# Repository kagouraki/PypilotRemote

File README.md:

# Pypilot Remote

## Overview

**Pypilot Remote** is a Wi-Fi remote control and display for the  
[pypilot](https://github.com/pypilot/pypilot) open-source marine autopilot by Sean D’Epagnier.

It connects to a pypilot server in client mode and provides a **clean, dedicated hardware interface**
to control the autopilot and display essential navigation and system information.

The project is currently housed in a **Raymarine ST70 autopilot display**, giving new life to legacy
marine hardware. The design is intentionally adaptable so it can be reused with other discontinued
or surplus commercial enclosures.

A future goal is a **custom 3D-printed enclosure**, which would make the project more accessible
without relying on expensive legacy hardware. This will require additional work around waterproof
screen mounting, buttons, and connectors.

---

## Hardware

- **MCU:** ESP32-S3 N16R8 with external antenna  
- **Display:** 3.47" transflective color LCD  
  - Resolution: 480×320  
  - Model: UEED035HV-RX40-L001B (Viewe)  
- **Input:** 9 physical pushbuttons (no touchscreen)
- **Power input:** 10–18 V DC
- **Programming:**  
  - USB (without opening the enclosure)  
  - OTA (Over-The-Air updates)

---

## Software & Design Tools

- **Firmware:** ESP32 (Arduino framework)
- **IDE:** Eclipse Sloeber
- **Hardware design:** KiCad v9
- **License:** GPL-3.0-only

---

## Features

- Connects to a pypilot server or creates an AP for configuration
- Autopilot **Auto / Standby** control
- Steering mode selection
- Course changes in Auto mode:
  - −1°, −10°, +1°, +10°
- Adjustable backlight for screen and buttons
- Light and dark UI themes
- Information screens:
  - Pypilot data
  - Device status
- Scrollable console log
- “Return to previous heading” Auto command
- Persistent configuration stored in EEPROM
- Robust Wi-Fi and TCP reconnection handling
- Visual Wi-Fi status indicator

---

## Button Functions

### Autopilot Control
- **Standby**  
  Disengages the autopilot

- **Auto**  
  Engages the autopilot and commands the current heading

- **Auto (long press > 3 s)**  
  Engages autopilot using the **previous heading command**

### Course Adjustment
- **−1** → Port 1°  
- **−10** → Port 10°  
- **+1** → Starboard 1°  
- **+10** → Starboard 10°

### Mode & Interface
- **Mode**  
  Cycles through available steering modes

- **Backlight**  
  Toggles backlight on/off

- **Backlight (long press > 10 s)**  
  Forces AP mode

- **Info**  
  Cycles through information screens and returns to home

- **Backlight + Mode (long press > 5 s)**  
  Restarts the Pypilot Remote

### Notes
- When **not on the home screen**, only **Auto** and **Standby** are active
- On the console log screen:
  - **+1 / +10** scroll up and down

---

## Connection Logic

1. On boot, the device attempts to connect to the configured Wi-Fi SSID  
   → Wi-Fi icon flashes **RED**
2. After the configured number of retries:
   - If unsuccessful → switches to **AP mode** (Wi-Fi icon **YELLOW**)
3. Once Wi-Fi is connected:
   - Tries to connect to the pypilot TCP server indefinitely  
   → Wi-Fi icon flashes **GREEN**
4. When connected to pypilot:
   - Wi-Fi icon becomes **solid GREEN**
   - Device is fully operational

---

## Configuration Web Interface

When in **AP mode**, access the configuration interface at:

```
http://192.168.4.1
```

### Available Settings

- **WiFi SSID** – Network to connect to
- **WiFi Password**
- **Max WiFi Retries** – Attempts before falling back to AP mode
- **Pypilot IP** – IP address of the pypilot server
- **TCP Port** – Default: `23322`
- **UDP Port** – Not used
- **Brightness (Backlight Off)** – 0–255
- **Brightness (Backlight On)** – 0–255
- **Key Backlight Brightness** – 0–255
- **Start Theme** – Theme when backlight is off
- **Backlight Theme** – Theme when backlight is on
- **Rescan Wi-Fi** – Refresh available networks
- **OTA Update** – Upload firmware `.bin` file

---

## Electrical Connections

The device uses **4 pins** from the SeatalkNG connector:

| Color | Signal |
|-----|-------|
| Red | +12 V |
| Black | GND |
| Blue | D+ |
| White | D− |

### Important Warning

⚠️ **DO NOT CONNECT TO A SEATALKNG NETWORK**

- Blue and white lines are **CAN-H / CAN-L**
- Connecting them to the ESP32 **will destroy the MCU**

### USB Programming (Optional)

For USB programming or debugging:
- Splice a USB cable
- Connect **D+**, **D−**, and **GND**
- A serial port will appear on the host computer

---

## Assembly

You can find the assembly guide here 
[assembly wiki](https://github.com/kagouraki/PypilotRemote/wiki/Assembly)

---

## Video

📺 **Demo video:**  

[Interface and funtionality video](https://youtu.be/A5Dgf8vR-sQ)

---

## License

This project is licensed under the  
**GNU General Public License v3.0 (GPL-3.0-only)**.

See the `LICENSE` file for details.

---

## Contributing

Contributions, improvements, and adaptations to other hardware platforms
are welcome — as long as they respect the GPL.

Let’s keep open source alive.

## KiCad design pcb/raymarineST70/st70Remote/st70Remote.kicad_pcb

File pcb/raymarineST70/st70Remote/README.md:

# PCB / Hardware Design

This directory contains the **PCB design files** for the **Pypilot Remote** hardware.

The board is designed using **KiCad v9** and is intended to be manufactured using standard PCB
fabrication and assembly services.

---

## Design Tools

- **EDA software:** KiCad v9  
- **Project files:** Native KiCad schematic and PCB files  
- **Units:** Metric

---

## Manufacturing

### PCB Fabrication
- The PCB was ordered and manufactured using **JLCPCB**

### Component Sourcing
- All electronic components were sourced from **LCSC**
- Component details and ordering information are provided in:

```
LCSCpartNum.csv
```

This file contains LCSC part numbers and additional information useful for ordering parts.

---

## Assembly Notes

### SeatalkNG Connector

The SeatalkNG connector is **not a standard off-the-shelf part**.

To populate it:
- Desolder one of the two SeatalkNG connectors from a **stock Raymarine ST70 PCB**
- Solder the recovered connector onto the **Pypilot Remote PCB**

This approach was chosen to ensure mechanical compatibility with the original enclosure.

---

### 3D Printed Parts

A **3D-printed adapter for the LCD screen** is required.

- The adapter files are located in the `3dparts/` directory
- It is used to correctly position and secure the display within the enclosure

---

### Double-Sided Assembly

- The PCB uses **components on both top and bottom layers**
- This may be more challenging for home assembly, but it is feasible

---

## Notes

- The PCB design is closely tied to the enclosure and mechanical layout
- Modifications may be required if adapting the design to a different housing

---

## License

The PCB design is released under the  
**GNU General Public License v3.0 (GPL-3.0-only)**.

See the `LICENSE` file in the root of the repository for details.

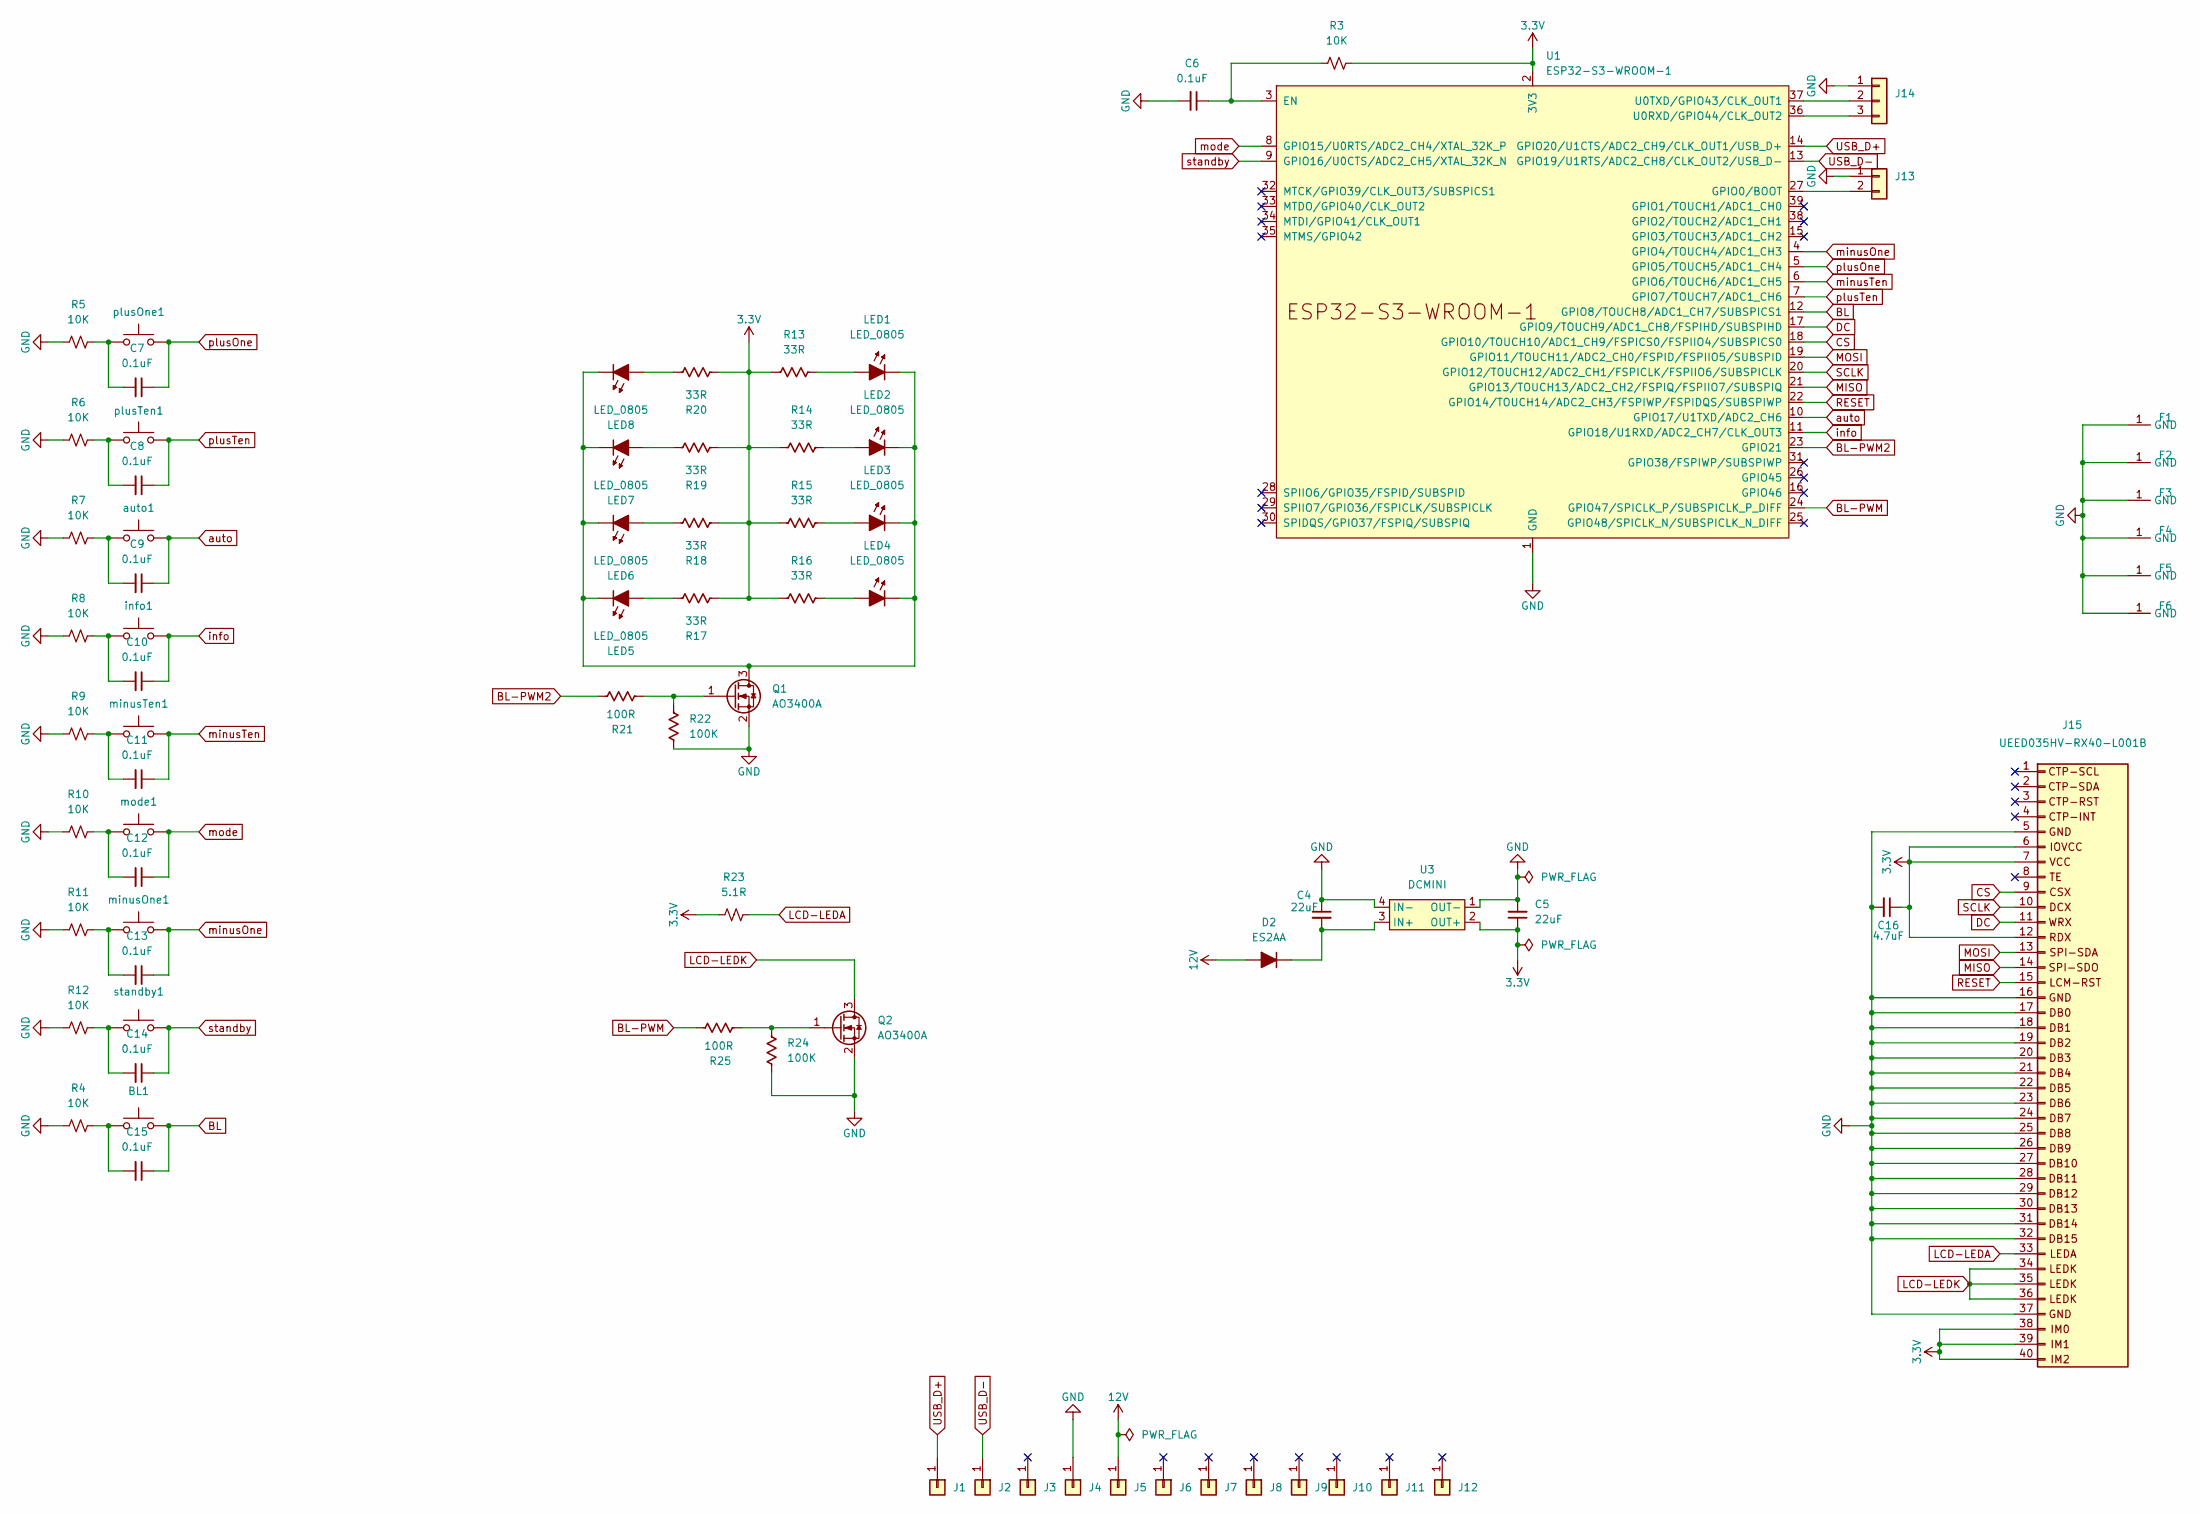
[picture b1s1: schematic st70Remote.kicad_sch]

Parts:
BL1: SMD_6.2x6.2mm_h7.0mm; Push_SMD_6.2x6.2mm; Mfg Part# 679-2384-2-ND
C4, C5: 22uF; C_1206_3216Metric_Pad1.42x1.75mm; Voltage 25V; Tolerance 10%
C6, C7, C8, C9, C10, C11, C12, C13, C14, C15: 0.1uF; C_0805_2012Metric; Voltage 25V; Tolerance 5%
C16: 4.7uF; C_0805_2012Metric; Voltage 25V; Tolerance 5%
D2: ES2AA; D_SMA
F1, F2, F3, F4, F5, F6: Harwin S1791-42R
J1, J2, J3, J4, J5, J6, J7, J8, J9, J10, J11, J12: Conn_01x01; 1x01_P2.54mm
J13: Conn_01x02; 1x02_P2.54mm
J14: Conn_01x03; 1x03_P2.54mm_Locking
J15: UEED035HV-RX40-L001B; XUNPU FPC-05F-40PH20
LED1, LED2, LED3, LED4, LED5, LED6, LED7, LED8: LED_0805; LED_0805_2012Metric
Q1, Q2: AO3400A; SOT-23
R3, R4, R5, R6, R7, R8, R9, R10, R11, R12: 10K; R_0805_2012Metric
R13, R14, R15, R16, R17, R18, R19, R20: 33R; R_0805_2012Metric
R21, R25: 100R; R_0805_2012Metric
R22, R24: 100K; R_0805_2012Metric
R23: 5.1R; R_0805_2012Metric
U1: ESP32-S3-WROOM-1; ESP32-S3-WROOM-1U
U3: DCMINI
auto1: SMD_6.2x6.2mm_h7.0mm; Push_SMD_6.2x6.2mm; Mfg Part# 679-2384-2-ND
info1: SMD_6.2x6.2mm_h7.0mm; Push_SMD_6.2x6.2mm; Mfg Part# 679-2384-2-ND
minusOne1: SMD_6.2x6.2mm_h7.0mm; Push_SMD_6.2x6.2mm; Mfg Part# 679-2384-2-ND
minusTen1: SMD_6.2x6.2mm_h7.0mm; Push_SMD_6.2x6.2mm; Mfg Part# 679-2384-2-ND
mode1: SMD_6.2x6.2mm_h7.0mm; Push_SMD_6.2x6.2mm; Mfg Part# 679-2384-2-ND
plusOne1: SMD_6.2x6.2mm_h7.0mm; Push_SMD_6.2x6.2mm; Mfg Part# 679-2384-2-ND
plusTen1: SMD_6.2x6.2mm_h7.0mm; Push_SMD_6.2x6.2mm; Mfg Part# 679-2384-2-ND
standby1: SMD_6.2x6.2mm_h7.0mm; Push_SMD_6.2x6.2mm; Mfg Part# 679-2384-2-ND

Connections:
3.3V: C5.1, C16.1, J15.6, J15.7, J15.12, J15.38, J15.39, J15.40, R3.1, R13.1, R14.1, R15.1, R16.1, R17.1, R18.1, R19.1, R20.1, R23.2, U1.2 (3V3), U3.2 (OUT+)
12V: D2.2 (A), J5.1
BL: BL1.2, C15.1, U1.12 (GPIO8/TOUCH8/ADC1_CH7/SUBSPICS1)
BL-PWM: R25.2, U1.24 (GPIO47/SPICLK_P/SUBSPICLK_P_DIFF)
BL-PWM2: R21.2, U1.23 (GPIO21)
CS: J15.9, U1.18 (GPIO10/TOUCH10/ADC1_CH9/FSPICS0/FSPIIO4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)
DC: J15.11, U1.17 (GPIO9/TOUCH9/ADC1_CH8/FSPIHD/SUBSPIHD)
GND: C4.1, C5.2, C6.2, C16.2, F1.1 (GND), F2.1 (GND), F3.1 (GND), F4.1 (GND), F5.1 (GND), F6.1 (GND), J4.1, J13.1, J14.1, J15.5, J15.16, J15.17, J15.18, J15.19, J15.20, J15.21, J15.22, J15.23, J15.24, J15.25, J15.26, J15.27, J15.28, J15.29, J15.30, J15.31, J15.32, J15.37, J15.41 (GND), Q1.2 (S), Q2.2 (S), R4.2, R5.2, R6.2, R7.2, R8.2, R9.2, R10.2, R11.2, R12.2, R22.2, R24.2, U1.1 (GND), U1.40 (GND), U1.41 (GND), U3.1 (OUT-), U3.4 (IN-)
LCD-LEDA: J15.33, R23.1
LCD-LEDK: J15.34, J15.35, J15.36, Q2.3 (D)
MISO: J15.14, U1.21 (GPIO13/TOUCH13/ADC2_CH2/FSPIQ/FSPIIO7/S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)
MOSI: J15.13, U1.19 (GPIO11/TOUCH11/ADC2_CH0/FSPID/FSPIIO5/S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)
unnamed: BL1.1, C15.2, R4.1
unnamed: C7.2, R5.1, plusOne1.1
unnamed: C8.2, R6.1, plusTen1.1
unnamed: C9.2, R7.1, auto1.1
unnamed: C10.2, R8.1, info1.1
unnamed: C11.2, R9.1, minusTen1.1
unnamed: C12.2, R10.1, mode1.1
unnamed: C13.2, R11.1, minusOne1.1
unnamed: C14.2, R12.1, standby1.1
unnamed: C4.2, D2.1 (K), U3.3 (IN+)
unnamed: J13.2, U1.27 (GPIO0/BOOT)
unnamed: J14.2, U1.37 (U0TXD/GPIO43/CLK_OUT1)
unnamed: J14.3, U1.36 (U0RXD/GPIO44/CLK_OUT2)
unnamed: LED1.2 (A), R13.2
unnamed: LED1.1 (K), LED2.1 (K), LED3.1 (K), LED4.1 (K), LED5.1 (K), LED6.1 (K), LED7.1 (K), LED8.1 (K), Q1.3 (D)
unnamed: LED2.2 (A), R14.2
unnamed: LED3.2 (A), R15.2
unnamed: LED4.2 (A), R16.2
unnamed: LED5.2 (A), R17.2
unnamed: LED6.2 (A), R18.2
unnamed: LED7.2 (A), R19.2
unnamed: LED8.2 (A), R20.2
unnamed: Q1.1 (G), R21.1, R22.1
unnamed: Q2.1 (G), R24.1, R25.1
unnamed: C6.1, R3.2, U1.3 (EN)
RESET: J15.15, U1.22 (GPIO14/TOUCH14/ADC2_CH3/FSPIWP/FSPIDQS/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)
SCLK: J15.10, U1.20 (GPIO12/TOUCH12/ADC2_CH1/FSPICLK/FSPIIO6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)
USB_D+: J1.1, U1.14 (GPIO20/U1CTS/ADC2_CH9/CLK_OUT1/USB_D+)
USB_D-: J2.1, U1.13 (GPIO19/U1RTS/ADC2_CH8/CLK_OUT2/USB_D-)
auto: C9.1, U1.10 (GPIO17/U1TXD/ADC2_CH6), auto1.2
info: C10.1, U1.11 (GPIO18/U1RXD/ADC2_CH7/CLK_OUT3), info1.2
minusOne: C13.1, U1.4 (GPIO4/TOUCH4/ADC1_CH3), minusOne1.2
minusTen: C11.1, U1.6 (GPIO6/TOUCH6/ADC1_CH5), minusTen1.2
mode: C12.1, U1.8 (GPIO15/U0RTS/ADC2_CH4/XTAL_32K_P), mode1.2
plusOne: C7.1, U1.5 (GPIO5/TOUCH5/ADC1_CH4), plusOne1.2
plusTen: C8.1, U1.7 (GPIO7/TOUCH7/ADC1_CH6), plusTen1.2
standby: C14.1, U1.9 (GPIO16/U0CTS/ADC2_CH5/XTAL_32K_N), standby1.2

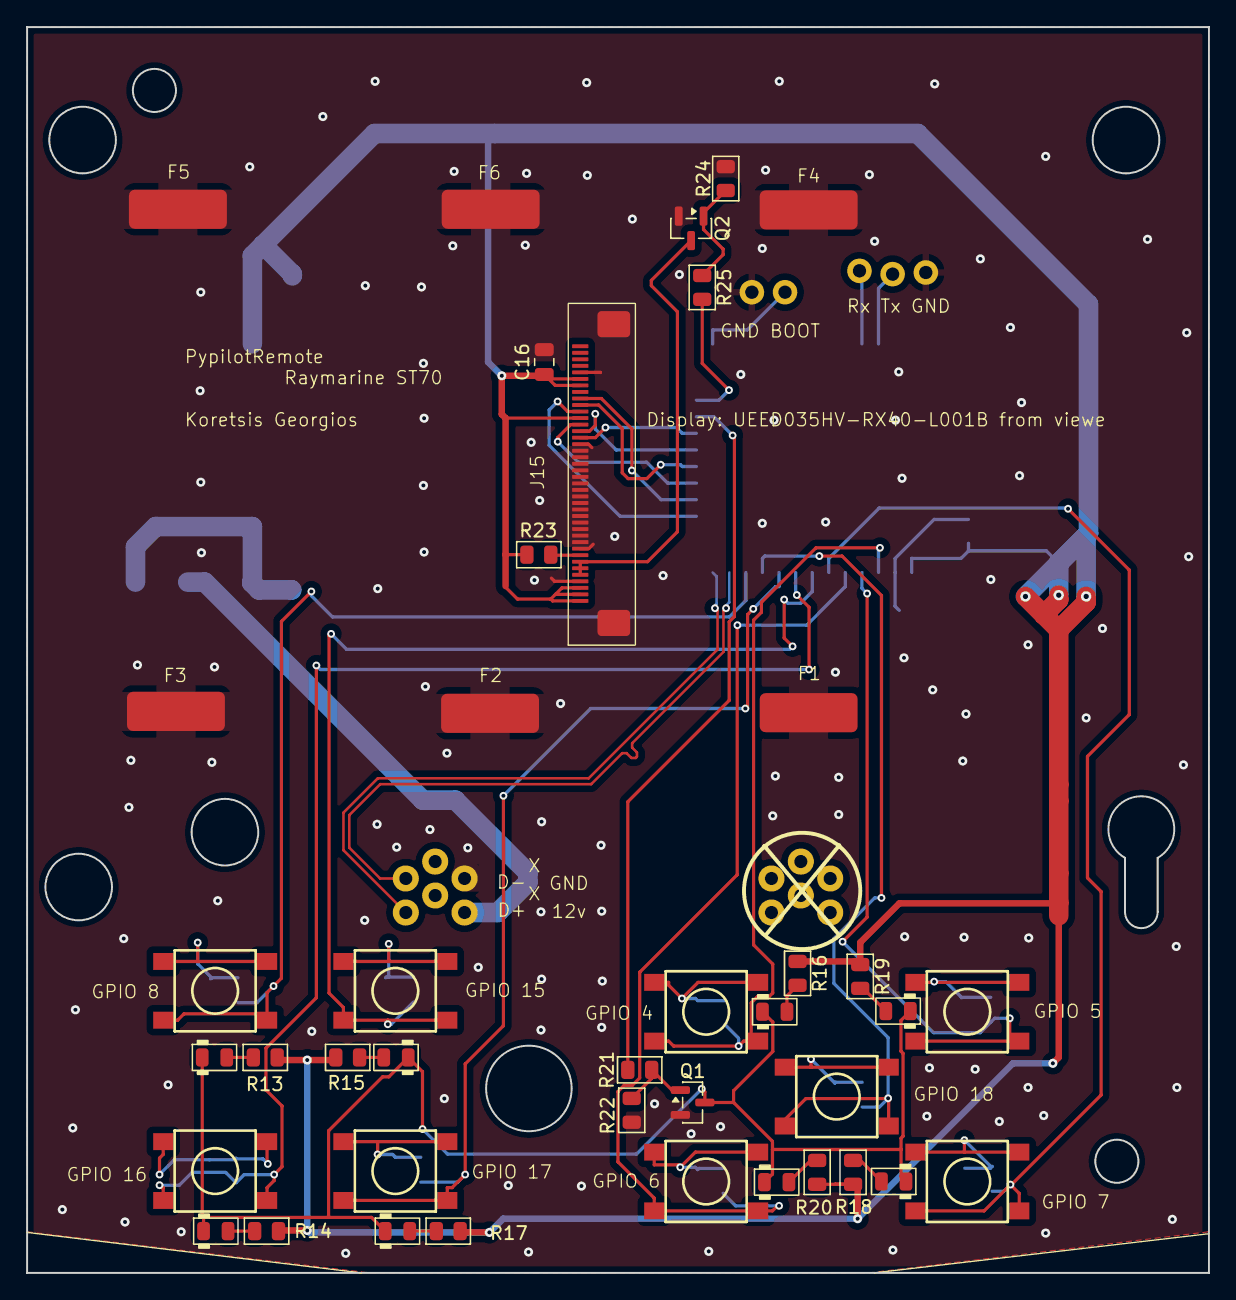
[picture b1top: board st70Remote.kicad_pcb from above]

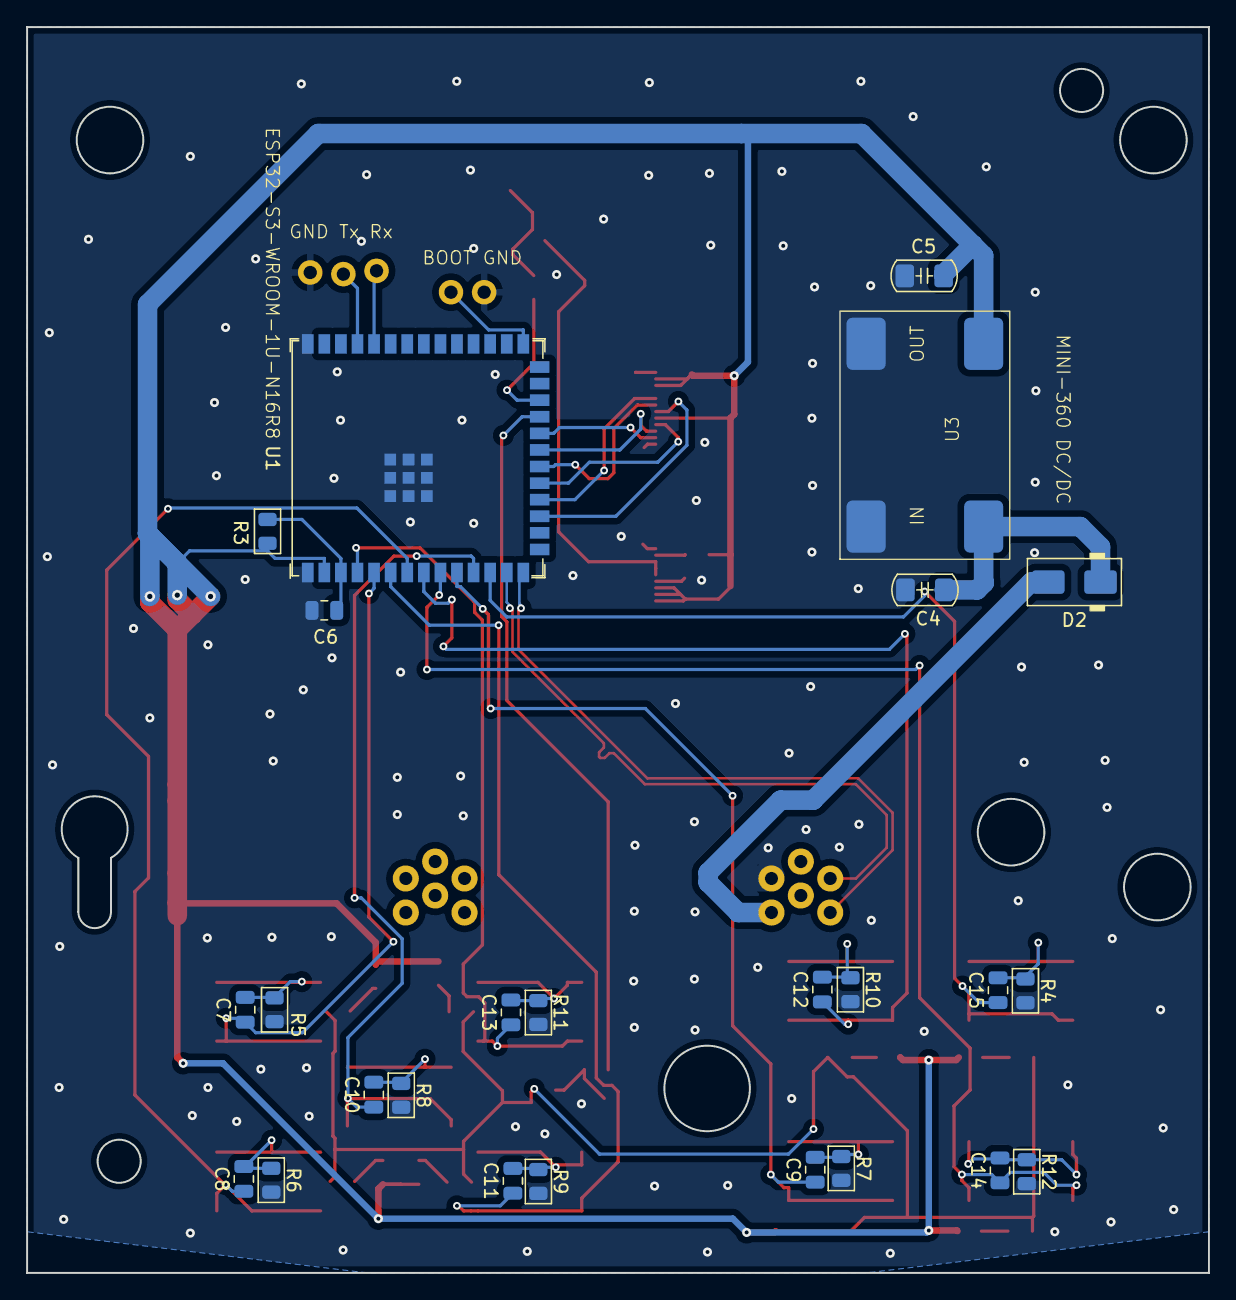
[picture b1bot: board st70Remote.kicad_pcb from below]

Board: 2 copper layers, 90.5 x 95.4 mm, 79 parts (27 on the bottom side), 49 nets.

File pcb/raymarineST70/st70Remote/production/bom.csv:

Designator,Footprint,Quantity,Value,LCSC Part #
"AUTO1, BL1, INFO1, MINUSONE1, MINUSTEN1, MODE1, PLUSONE1, PLUSTEN1, STANDBY1",Push_SMD_6.2x6.2mm,9,SMD_6.2x6.2mm_h7.0mm,
"C10, C11, C12, C13, C14, C15, C6, C7, C8, C9",0805,10,0.1uF,
C16,0805,1,4.7uF,
"C4, C5",1206,2,22uF,
D2,D_SMA,1,ES2AA,
"F1, F2, F3, F4, F5, F6",Harwin S1791-42R,6,~,
"J1, J10, J11, J12, J2, J3, J4, J5, J6, J7, J8, J9",1x01_P2.54mm,12,Conn_01x01,
J13,1x02_P2.54mm,1,Conn_01x02,
J14,1x03_P2.54mm_Locking,1,Conn_01x03,
J15,XUNPU FPC-05F-40PH20,1,UEED035HV-RX40-L001B,
"LED1, LED2, LED3, LED4, LED5, LED6, LED7, LED8",0805,8,LED_0805,
"Q1, Q2",SOT-23,2,AO3400A,
"R10, R11, R12, R3, R4, R5, R6, R7, R8, R9",0805,10,10K,
"R13, R14, R15, R16, R17, R18, R19, R20",0805,8,33R,
"R21, R25",0805,2,100R,
"R22, R24",0805,2,100K,
R23,0805,1,5.1R,
U1,ESP32-S3-WROOM-1U,1,ESP32-S3-WROOM-1,
U3,DCMINI,1,DCMINI,

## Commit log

2026-01-31 Initial File commit
2026-01-31 initial file commint Try2
2026-01-31 initial file commit try3
2026-01-31 Readme and files
2026-01-31 Readme and files try2
2026-01-31 Fix image paths in README.md
    Updated image paths to use relative paths from the parent directory.
2026-01-31 Add assembly section with link to wiki
    Added assembly guide link to README.
2026-02-04 Add demo video link to README
